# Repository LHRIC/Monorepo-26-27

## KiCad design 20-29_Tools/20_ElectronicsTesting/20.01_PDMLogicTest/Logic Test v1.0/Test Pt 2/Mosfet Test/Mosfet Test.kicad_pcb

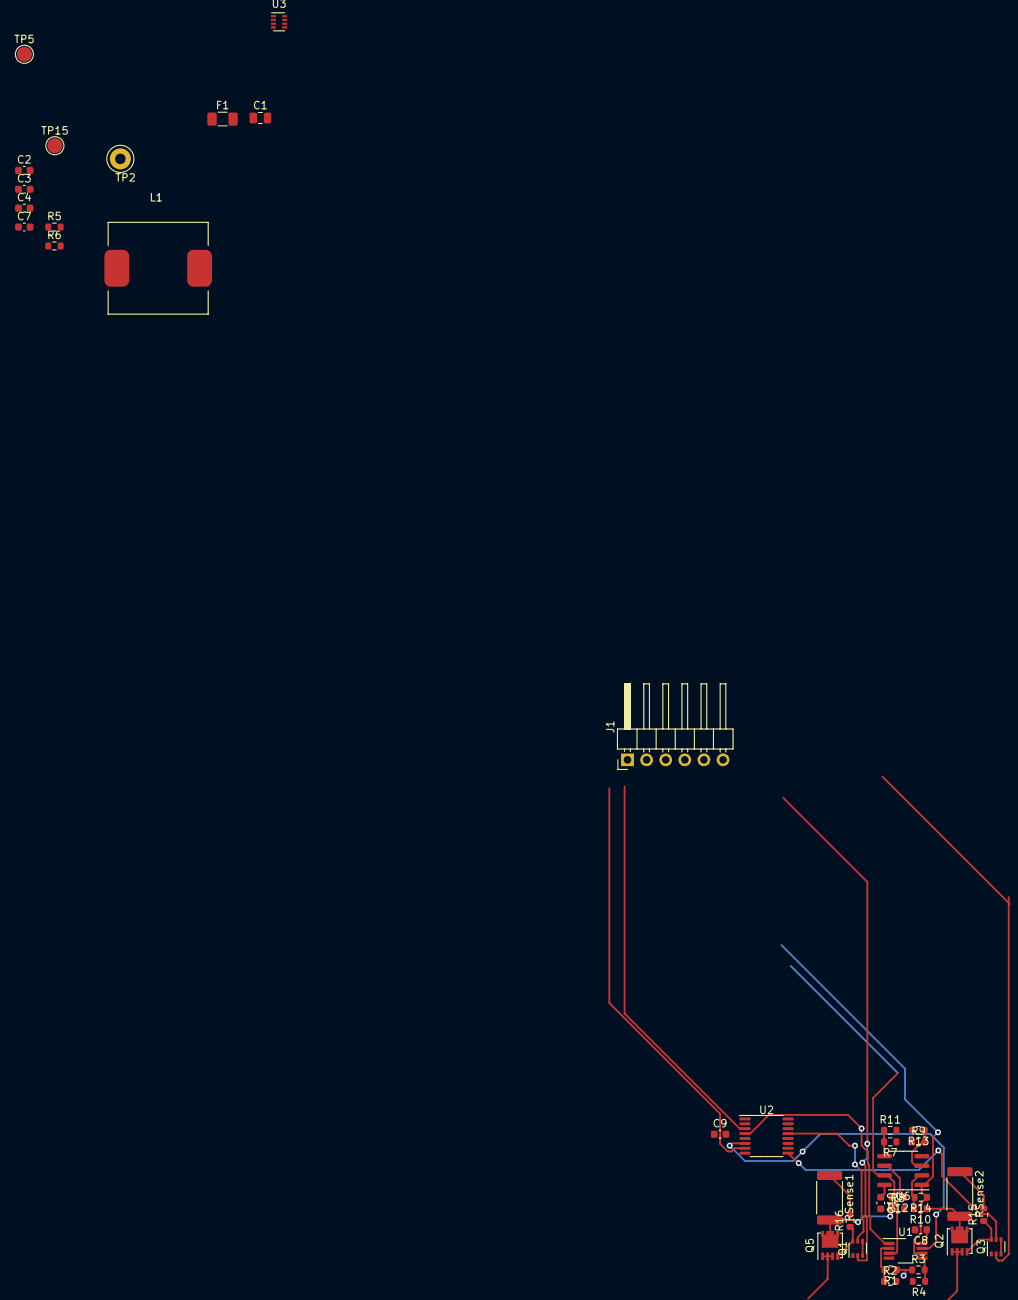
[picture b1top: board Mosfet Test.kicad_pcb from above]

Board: 2 copper layers, 40 parts (0 on the bottom side), 32 nets.

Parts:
C1: 10uF; C_0805_2012Metric
C2, C4: 0.1uF; C_0603_1608Metric
C3: 33nF; C_0603_1608Metric
C7: 47uF; C_0603_1608Metric
C8, C9, C10: C_Small; C_0603_1608Metric
F1: 750mA; Fuse_1206_3216Metric
J1: Conn_01x06_Pin; PinHeader_1x06_P2.54mm_Horizontal
L1: 5.6uH; HCMA1305-5R6-R
Q1, Q3: DMN63D8LDW; SOT-363_SC-70-6
Q2, Q5: SiS443DN; Vishay_PowerPAK_1212-8_Single
R1, R2, R3, R4, R7, R8, R9, R10, R11, R12, R13, R14: R_Small; R_0603_1608Metric
R5: 52.3k; R_0603_1608Metric
R6: 10k; R_0603_1608Metric
R15, R16: 100k; R_0603_1608Metric
RSense1, RSense2: R_Small; R_2512_6332Metric
TP2: TestPoint; TestPoint_Loop_D3.50mm_Drill1.4mm_Beaded
TP5, TP15: TP; TestPoint_Pad_D2.0mm
U1: TLV7012DGKR; VSSOP-8_3.0x3.0mm_P0.65mm
U2: CD4044B; TSSOP-16_4.4x5mm_P0.65mm
U3: TPS62933; SOT-583
U6: Opamp_Dual; SOIC-8_3.9x4.9mm_P1.27mm

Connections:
+5V: C8.1, C9.1, C10.1, F1.2, R1.1, R3.1, TP15.1, U1.8 (V+), U2.5 (Enable), U2.16 (V+), U6.8 (V+)
+12V: C1.1, C2.1, R7.1, R9.1, R15.2, R16.2, RSense1.1, RSense2.1, TP2.1, TP5.1, U3.3 (VIN)
/Drain: Q5.5 (D), R8.1, RSense1.2
/Fault: Q3.5 (G), U2.9 (Q)
/Load+: Q2.1 (S), Q2.2 (S), Q2.3 (S)
/Source: Q5.1 (S), Q5.2 (S), Q5.3 (S)
CS1: J1.3, R12.2, U1.3 (+), U6.7
CS2: J1.6, R14.1, U1.6 (-), U6.1
EN1: J1.2, Q1.2 (G)
EN2: J1.5, Q3.2 (G)
GND: C1.2, C2.2, C3.2, C7.2, C8.2, C9.2, C10.2, Q1.1 (S), Q3.1 (S), R2.2, R4.2, R6.2, R11.2, R13.2, U1.4 (V-), U2.8 (V-), U3.4 (GND), U6.4 (V-)
unnamed: C7.1, F1.1, L1.2, R5.1
unnamed: Q1.6 (D), Q5.4 (G), R16.1
unnamed: Q1.5 (G), U2.13 (Q)
unnamed: Q1.3 (D), Q1.4 (S)
unnamed: Q2.5 (D), R10.1, RSense2.2
unnamed: Q2.4 (G), Q3.6 (D), R15.1
unnamed: Q3.3 (D), Q3.4 (S)
unnamed: R1.2, R2.1, U1.2 (-)
unnamed: R3.2, R4.1, U1.5 (+)
unnamed: U1.1, U2.4 (R)
unnamed: U1.7, U2.6 (R)
unnamed: C4.1, U3.6 (BST)
unnamed: R5.2, R6.1, U3.8 (FB)
unnamed: C3.1, U3.7 (SS)
unnamed: C4.2, L1.1, U3.5 (SW)
unnamed: R9.2, R13.1, U6.3 (+)
unnamed: R10.2, R14.2, U6.2 (-)
unnamed: R7.2, R11.1, U6.5 (+)
unnamed: R8.2, R12.1, U6.6 (-)
Reset1: J1.1, U2.3 (S)
Reset2: J1.4, U2.7 (S)

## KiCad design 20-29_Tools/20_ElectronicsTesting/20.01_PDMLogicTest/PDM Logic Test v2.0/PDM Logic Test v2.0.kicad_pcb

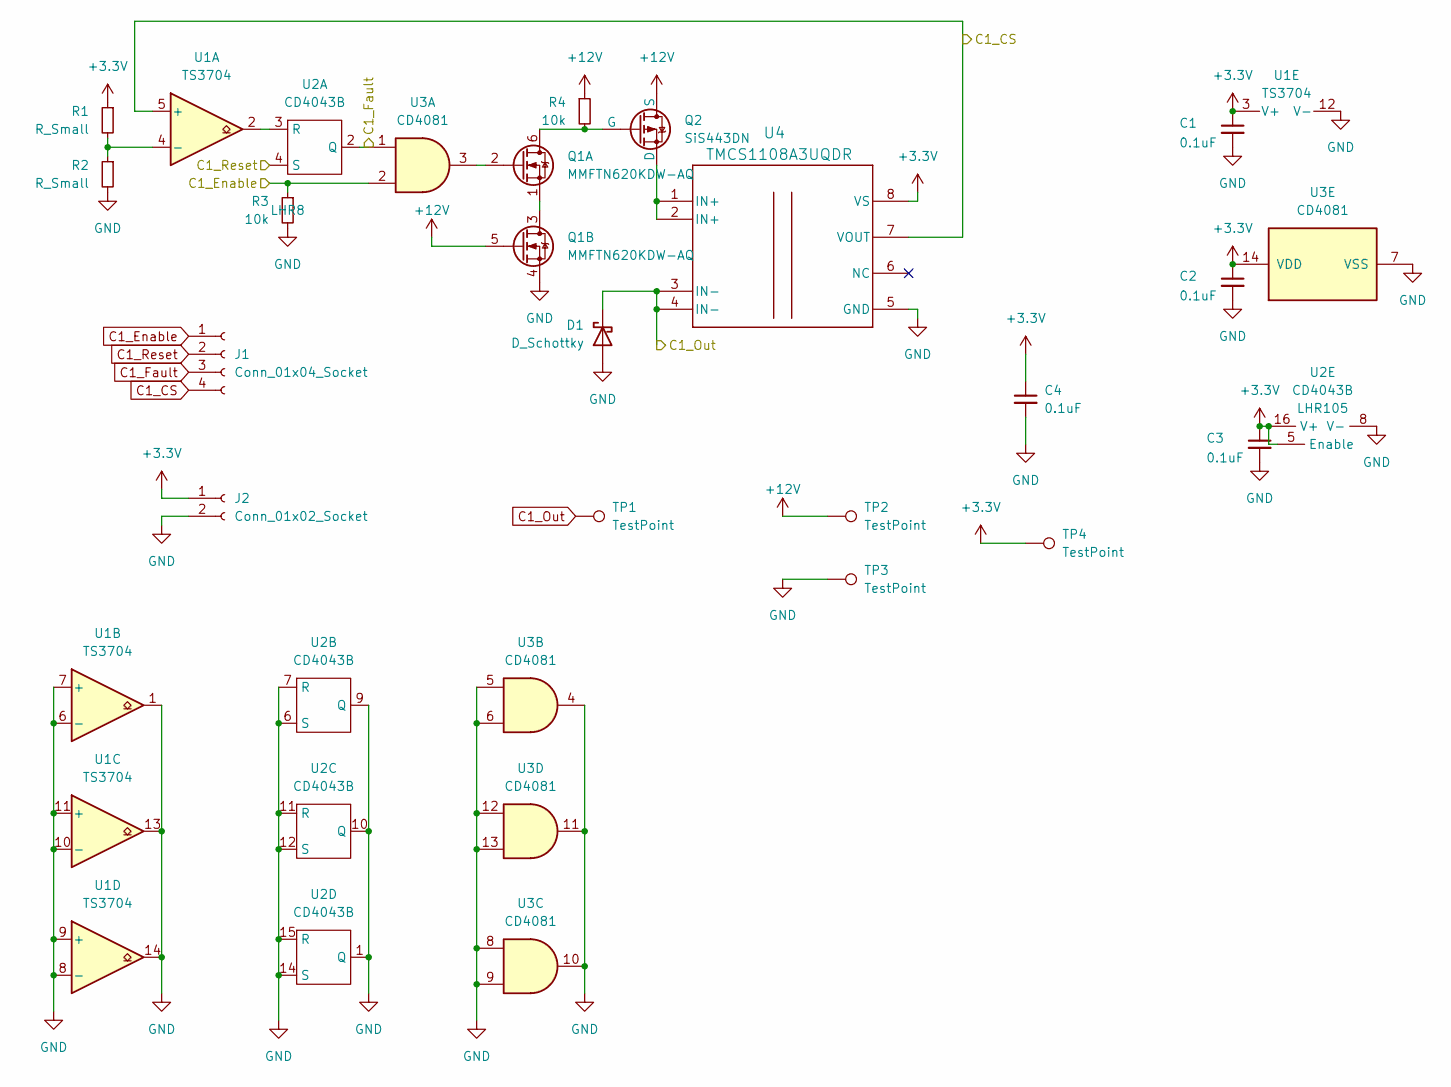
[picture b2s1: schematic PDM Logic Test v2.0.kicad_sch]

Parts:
C1, C2, C3, C4: 0.1uF; C_0603_1608Metric; LCSC C1591
D1: D_Schottky; D_SOD-523; LCSC C3758469
J1: Conn_01x04_Socket; PinHeader_1x04_P2.54mm_Vertical
J2: Conn_01x02_Socket; PinHeader_1x02_P2.54mm_Vertical
Q1: MMFTN620KDW-AQ; SOT-363_SC-70-6; LCSC C6226911
Q2: SiS443DN; Vishay_PowerPAK_1212-8_Single; LCSC C48586476
R1, R2: R_Small; R_0603_1608Metric
R3, R4: 10k; R_0603_1608Metric; LCSC C2479067
TP1, TP2: TestPoint; TestPoint_THTPad_D3.0mm_Drill1.5mm
TP3, TP4: TestPoint; TestPoint_Pad_D1.5mm
U1: TS3704; TSSOP-14_4.4x5mm_P0.65mm; LCSC C75832
U2: CD4043B; SOIC-16_3.9x9.9mm_P1.27mm
U3: CD4081; TSSOP-14_4.4x5mm_P0.65mm
U4: TMCS1108A3UQDR; SOIC-8_3.9x4.9mm_P1.27mm; LCSC C3684263

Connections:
+3.3V: C1.1, C2.1, C3.1, C4.1, J2.1, R1.1, TP4.1, U1.3 (V+), U2.5 (Enable), U2.16 (V+), U3.14 (VDD), U4.8 (VS)
+12V: Q1.5 (G), Q2.1 (S), Q2.2 (S), Q2.3 (S), R4.1, TP2.1
C1_CS: J1.4, U1.5 (+), U4.7 (VOUT)
C1_Enable: J1.1, R3.1, U3.2
C1_Fault: J1.3, U2.2 (Q), U3.1
C1_Out: D1.1 (K), TP1.1, U4.3 (IN-), U4.4 (IN-)
C1_Reset: J1.2, U2.4 (S)
GND: C1.2, C2.2, C3.2, C4.2, D1.2 (A), J2.2, Q1.4 (S), R2.2, R3.2, TP3.1, U1.1, U1.6 (-), U1.7 (+), U1.8 (-), U1.9 (+), U1.10 (-), U1.11 (+), U1.12 (V-), U1.13, U1.14, U2.1 (Q), U2.6 (S), U2.7 (R), U2.8 (V-), U2.9 (Q), U2.10 (Q), U2.11 (R), U2.12 (S), U2.14 (S), U2.15 (R), U3.4, U3.5, U3.6, U3.7 (VSS), U3.8, U3.9, U3.10, U3.11, U3.12, U3.13, U4.5 (GND)
unnamed: Q1.6 (D), Q2.4 (G), R4.2
unnamed: Q1.2 (G), U3.3
unnamed: Q1.1 (S), Q1.3 (D)
unnamed: Q2.5 (D), U4.1 (IN+), U4.2 (IN+)
unnamed: R1.2, R2.1, U1.4 (-)
unnamed: U1.2, U2.3 (R)

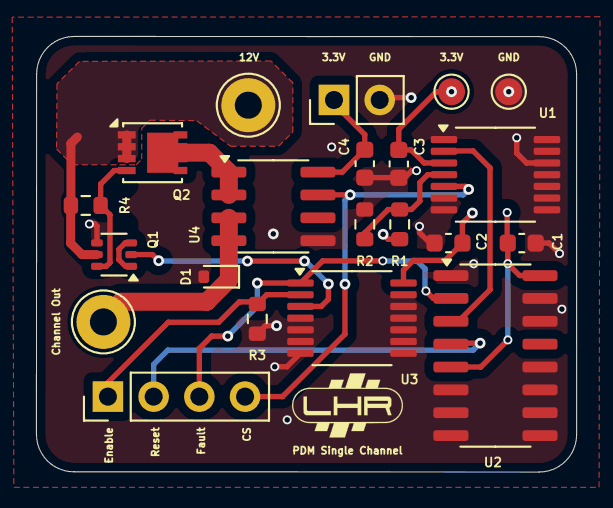
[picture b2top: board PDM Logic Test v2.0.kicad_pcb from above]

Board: 4 copper layers, 30.0 x 24.2 mm, 21 parts (0 on the bottom side), 14 nets.

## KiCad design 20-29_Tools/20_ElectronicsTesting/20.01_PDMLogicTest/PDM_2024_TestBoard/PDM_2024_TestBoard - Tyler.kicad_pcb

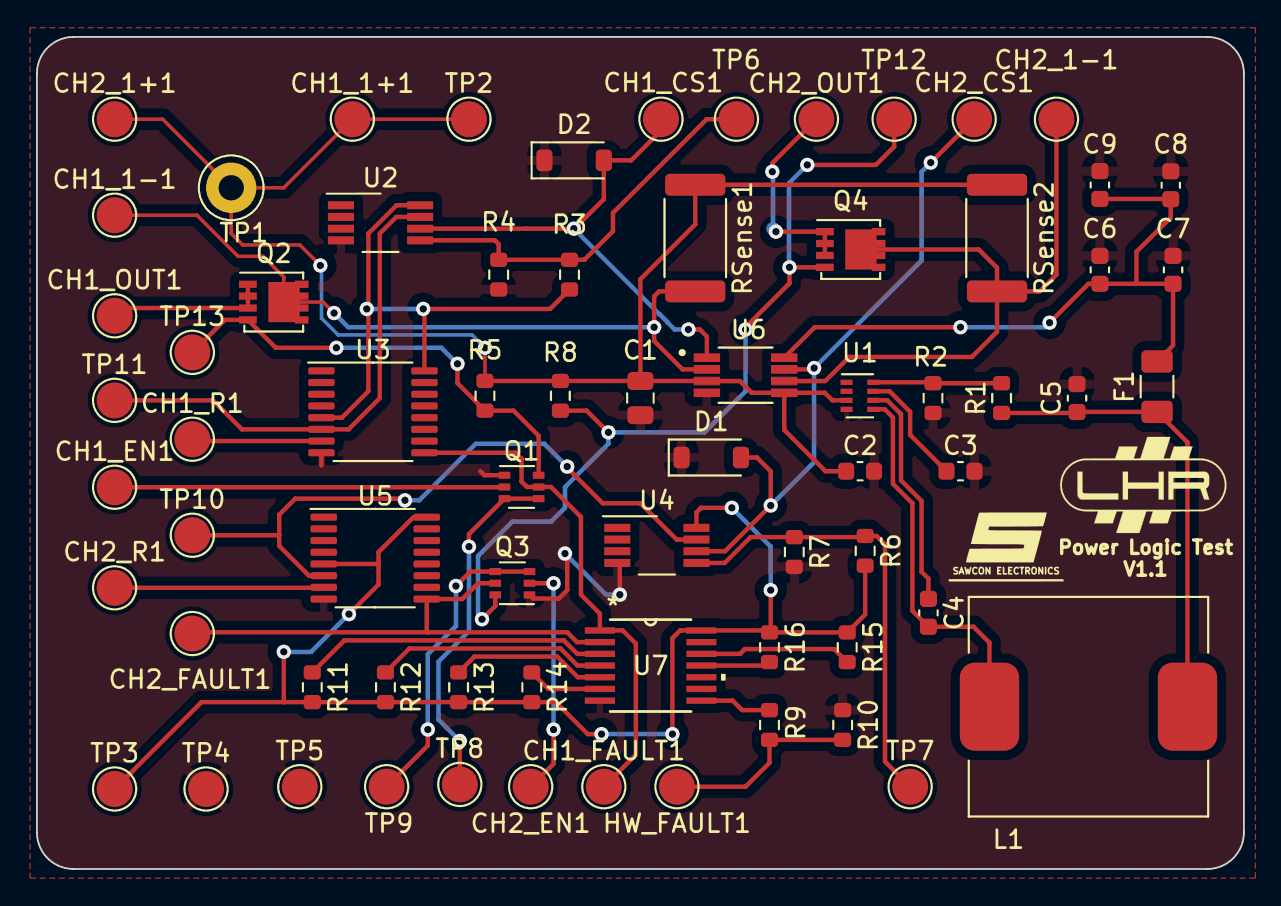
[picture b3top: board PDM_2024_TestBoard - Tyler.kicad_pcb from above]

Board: 4 copper layers, 67.1 x 46.2 mm, 70 parts (0 on the bottom side), 36 nets.

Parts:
C1: 10uF; C_0805_2012Metric
C2, C4: 0.1uF; C_0603_1608Metric
C3: 33nF; C_0603_1608Metric
C5: 47uF; C_0603_1608Metric
C6, C7, C8, C9: C_Small; C_0603_1608Metric
CH1_1+1, CH1_1-1, CH1_CS1, CH1_EN1, CH1_FAULT1, CH1_OUT1, CH1_R1, CH2_1+1, CH2_1-1, CH2_CS1, CH2_EN1, CH2_FAULT1, CH2_OUT1, CH2_R1: TP; TestPoint_Pad_D2.0mm
D1, D2: D_Zener; D_SOD-123
F1: 750mA; Fuse_1206_3216Metric
HW_FAULT1: TP; TestPoint_Pad_D2.0mm
L1: 5.6uH; HCMA1305-5R6-R
Q1, Q3: DMN63D8LDW; SOT-363_SC-70-6
Q2, Q4: SiS443DN; Vishay_PowerPAK_1212-8_Single
R1: 52.3k; R_0603_1608Metric
R2, R9, R11, R12, R13, R14, R15, R16: 10k; R_0603_1608Metric
R3, R4, R6, R7: R_Small; R_0603_1608Metric
R5, R8: 100k; R_0603_1608Metric
R10: 16k; R_0603_1608Metric
RSense1, RSense2: R_Small; R_2512_6332Metric
TP1: TestPoint; TestPoint_Loop_D3.50mm_Drill1.4mm_Beaded
TP2, TP3, TP4, TP5, TP6, TP7, TP8, TP9, TP10, TP11, TP12, TP13: TP; TestPoint_Pad_D2.0mm
U1: TPS62933; SOT-583
U2, U4: TLV7012DGKR; VSSOP-8_3.0x3.0mm_P0.65mm
U3, U5: CD4044B; TSSOP-16_4.4x5mm_P0.65mm
U6: INA2180A1IDGKT; SOP65P490X110-8N
U7: CD74HC30PWR; PW14

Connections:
+5V: C6.1, C7.1, C8.1, C9.1, F1.2, R3.2, R6.2, R11.2, R12.2, R13.2, R14.2, R15.1, R16.1, TP3.1, U2.8 (V+), U3.5 (Enable), U3.16 (V+), U4.8 (V+), U5.5 (Enable), U5.16 (V+), U6.8 (VS), U7.14 (VCC)
CH1_1+: C1.1, C2.1, CH1_1+1.1, CH2_1+1.1, R5.2, R8.2, RSense1.1, RSense2.1, TP1.1, TP2.1, U1.3 (VIN), U6.3 (IN+1), U6.5 (IN+2)
CH1_1-: CH1_1-1.1, Q2.5 (D), RSense1.2, U6.2 (IN-1)
CH1_CS: CH1_CS1.1, D2.2 (A), U2.6 (-), U6.1 (OUT1)
CH1_EN: CH1_EN1.1, Q1.2 (G)
CH1_Fault: CH1_FAULT1.1, Q1.5 (G), U3.9 (Q), U7.1 (A)
CH1_OUT: CH1_OUT1.1, Q2.1 (S), Q2.2 (S), Q2.3 (S)
CH1_R: CH1_R1.1, U3.7 (S)
CH2_1-: CH2_1-1.1, Q4.5 (D), RSense2.2, U6.6 (IN-2)
CH2_CS: CH2_CS1.1, D1.2 (A), U4.6 (-), U6.7 (OUT2)
CH2_EN: CH2_EN1.1, Q3.2 (G)
CH2_Fault: CH2_FAULT1.1, Q3.5 (G), U5.9 (Q), U7.2 (B)
CH2_OUT: CH2_OUT1.1, Q4.1 (S), Q4.2 (S), Q4.3 (S)
CH2_R: CH2_R1.1, U5.7 (S)
GND: C1.2, C2.2, C3.2, C5.2, C6.2, C7.2, C8.2, C9.2, D1.1 (K), D2.1 (K), Q1.1 (S), Q3.1 (S), R2.2, R4.2, R7.2, R10.1, TP4.1, TP5.1, U1.4 (GND), U2.4 (V-), U3.8 (V-), U4.4 (V-), U5.8 (V-), U6.4 (GND), U7.7 (GND)
HW1_Fault: HW_FAULT1.1, R9.1, R10.2
unnamed: C5.1, F1.1, L1.2, R1.1
unnamed: Q1.6 (D), Q2.4 (G), R5.1, TP13.1
unnamed: Q1.3 (D), Q1.4 (S), TP8.1
unnamed: Q3.6 (D), Q4.4 (G), R8.1, TP12.1
unnamed: Q3.3 (D), Q3.4 (S), TP9.1
unnamed: C4.1, U1.6 (BST)
unnamed: R1.2, R2.1, U1.8 (FB)
unnamed: C3.1, U1.7 (SS)
unnamed: C4.2, L1.1, U1.5 (SW)
unnamed: R3.1, R4.1, TP6.1, U2.5 (+)
unnamed: TP11.1, U2.7, U3.6 (R)
unnamed: R6.1, R7.1, TP7.1, U4.5 (+)
unnamed: TP10.1, U4.7, U5.6 (R)
unnamed: R9.2, U7.8 (*Y)
unnamed: R11.1, U7.3 (C)
unnamed: R12.1, U7.4 (D)
unnamed: R13.1, U7.5 (E)
unnamed: R14.1, U7.6 (F)
unnamed: R16.2, U7.11 (G)
unnamed: R15.2, U7.12 (H)

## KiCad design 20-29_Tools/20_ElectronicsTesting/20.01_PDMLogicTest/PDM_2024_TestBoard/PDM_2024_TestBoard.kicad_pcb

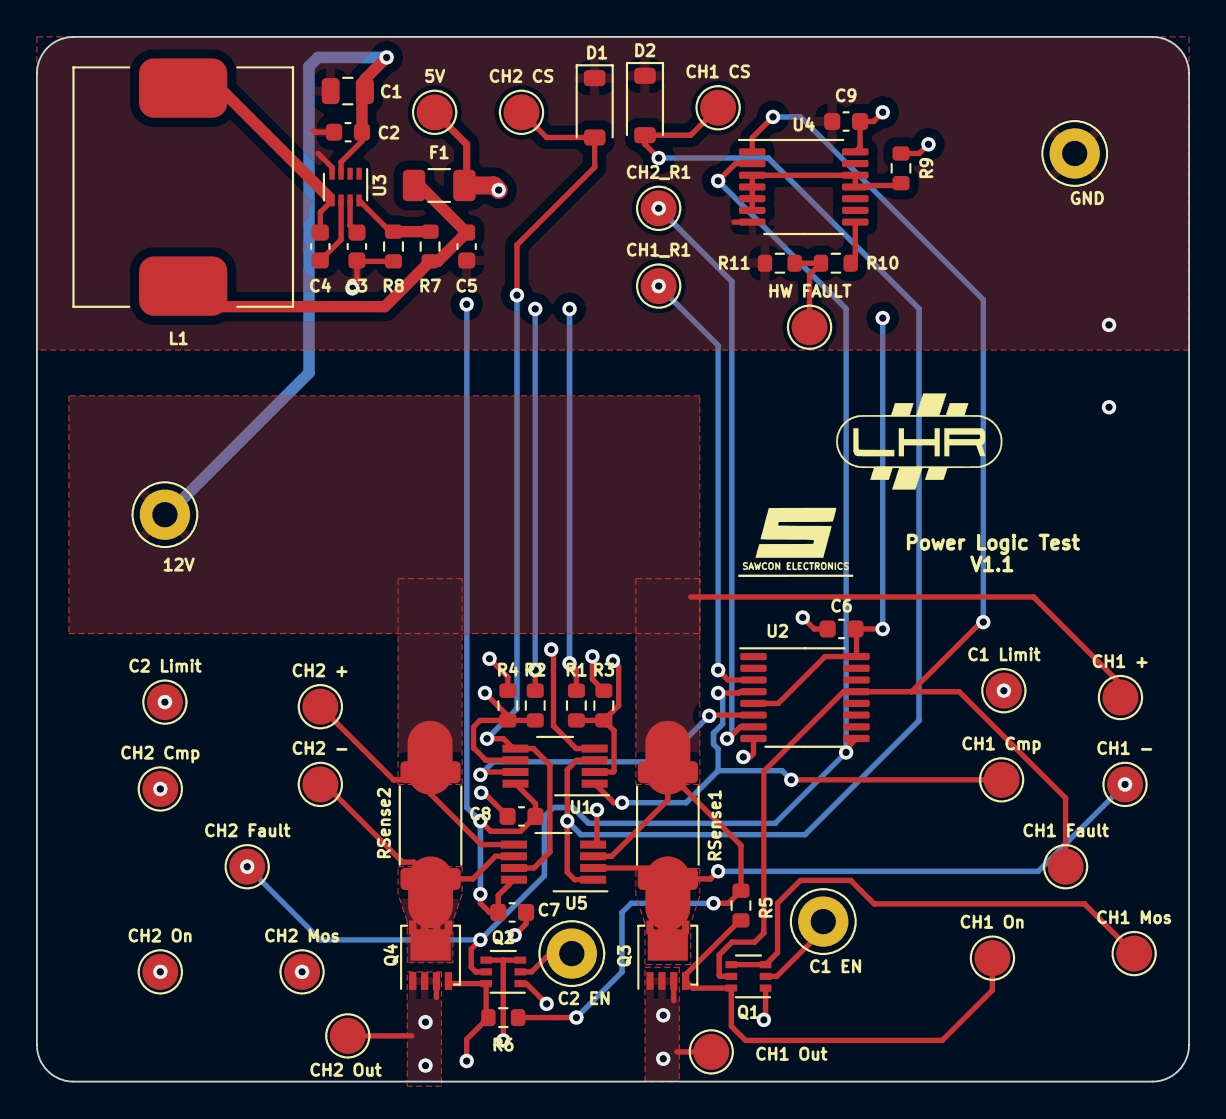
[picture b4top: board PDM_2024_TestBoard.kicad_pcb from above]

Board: 4 copper layers, 64.0 x 58.0 mm, 61 parts (0 on the bottom side), 31 nets.

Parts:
5V: TP; TestPoint_Pad_D2.0mm
12V: TestPoint; TestPoint_Loop_D3.50mm_Drill1.4mm_Beaded
C1: 10uF; C_0805_2012Metric
C1 EN, C2 EN: TestPoint; TestPoint_Loop_D3.50mm_Drill1.4mm_Beaded
C1 Limit, C2 Limit: TP; TestPoint_Pad_D2.0mm
C2, C4: 0.1uF; C_0603_1608Metric
C3: 33nF; C_0603_1608Metric
C5: 47uF; C_0603_1608Metric
C6, C7, C8, C9: C_Small; C_0603_1608Metric
CH1 +, CH1 -, CH1 CS, CH1 Cmp, CH1 Fault, CH1 Mos, CH1 On, CH1 Out, CH1_R1, CH2 +, CH2 -, CH2 CS, CH2 Cmp, CH2 Fault, CH2 Mos, CH2 On, CH2 Out, CH2_R1: TP; TestPoint_Pad_D2.0mm
D1, D2: D_Zener; D_SOD-123
F1: 750mA; Fuse_1206_3216Metric
GND: GND; TestPoint_Loop_D3.50mm_Drill1.4mm_Beaded
HW FAULT: TP; TestPoint_Pad_D2.0mm
L1: 5.6uH; HCMA1305-5R6-R
Q1, Q2: DMN63D8LDW; SOT-363_SC-70-6
Q3, Q4: SiS443DN; Vishay_PowerPAK_1212-8_Single
R1, R2, R3, R4: R_Small; R_0603_1608Metric
R5, R6: 100k; R_0603_1608Metric
R7: 52.3k; R_0603_1608Metric
R8, R9, R10: 10k; R_0603_1608Metric
R11: 16k; R_0603_1608Metric
RSense1, RSense2: R_Small; R_2512_6332Metric
U1: TLV7012DGKR; VSSOP-8_3.0x3.0mm_P0.65mm
U2: CD4044B; TSSOP-16_4.4x5mm_P0.65mm
U3: TPS62933; SOT-583
U4: CD74HC30PWR; TSSOP-14_4.4x5mm_P0.65mm
U5: INA2180A1IDGKT; VSSOP-8_3.0x3.0mm_P0.65mm

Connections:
+5V: 5V.1, C6.1, C7.1, C8.1, C9.2, F1.2, R1.2, R2.2, R9.1, U1.8 (V+), U2.5 (Enable), U2.16 (V+), U4.14 (VCC), U5.8 (VS)
+12V: 12V.1, C1.1, C2.1, CH1 +.1, CH2 +.1, R5.2, R6.2, RSense1.1, RSense2.1, U3.3 (VIN), U5.3 (IN+1), U5.5 (IN+2)
CH1-: CH1 -.1, Q3.5 (D), RSense1.2, U5.2 (IN-1)
CH1_CS: CH1 CS.1, D2.2 (A), U1.3 (+), U5.1 (OUT1)
CH1_EN: C1 EN.1, Q1.2 (G)
CH1_Fault: CH1 Fault.1, Q1.5 (G), U2.13 (Q), U4.1 (A)
CH1_OUT: CH1 Out.1, Q3.1 (S), Q3.2 (S), Q3.3 (S)
CH1_R: CH1_R1.1, U2.3 (S)
CH2-: CH2 -.1, Q4.5 (D), RSense2.2, U5.6 (IN-2)
CH2_CS: CH2 CS.1, D1.2 (A), U1.5 (+), U5.7 (OUT2)
CH2_EN: C2 EN.1, Q2.2 (G)
CH2_Fault: CH2 Fault.1, Q2.5 (G), U2.9 (Q), U4.2 (B)
CH2_OUT: CH2 Out.1, Q4.1 (S), Q4.2 (S), Q4.3 (S)
CH2_R: CH2_R1.1, U2.7 (S)
GND: C1.2, C2.2, C3.2, C5.2, C6.2, C7.2, C8.2, C9.1, D1.1 (K), D2.1 (K), GND.1, Q1.1 (S), Q2.1 (S), R3.2, R4.2, R8.2, R11.1, U1.4 (V-), U2.8 (V-), U3.4 (GND), U4.7 (GND), U5.4 (GND)
HW_Fault: HW FAULT.1, R10.1, R11.2
unnamed: C5.1, F1.1, L1.2, R7.1
unnamed: CH1 On.1, Q1.6 (D), Q3.4 (G), R5.1
unnamed: CH1 Mos.1, Q1.3 (D), Q1.4 (S)
unnamed: CH2 On.1, Q2.6 (D), Q4.4 (G), R6.1
unnamed: CH2 Mos.1, Q2.3 (D), Q2.4 (S)
unnamed: C1 Limit.1, R1.1, R3.1, U1.2 (-)
unnamed: C2 Limit.1, R2.1, R4.1, U1.6 (-)
unnamed: CH1 Cmp.1, U1.1, U2.4 (R)
unnamed: CH2 Cmp.1, U1.7, U2.6 (R)
unnamed: C4.1, U3.6 (BST)
unnamed: R7.2, R8.1, U3.8 (FB)
unnamed: C3.1, U3.7 (SS)
unnamed: C4.2, L1.1, U3.5 (SW)
unnamed: R10.2, U4.8 (*Y)
unnamed: R9.2, U4.3 (C), U4.4 (D), U4.5 (E), U4.6 (F), U4.11 (G), U4.12 (H)

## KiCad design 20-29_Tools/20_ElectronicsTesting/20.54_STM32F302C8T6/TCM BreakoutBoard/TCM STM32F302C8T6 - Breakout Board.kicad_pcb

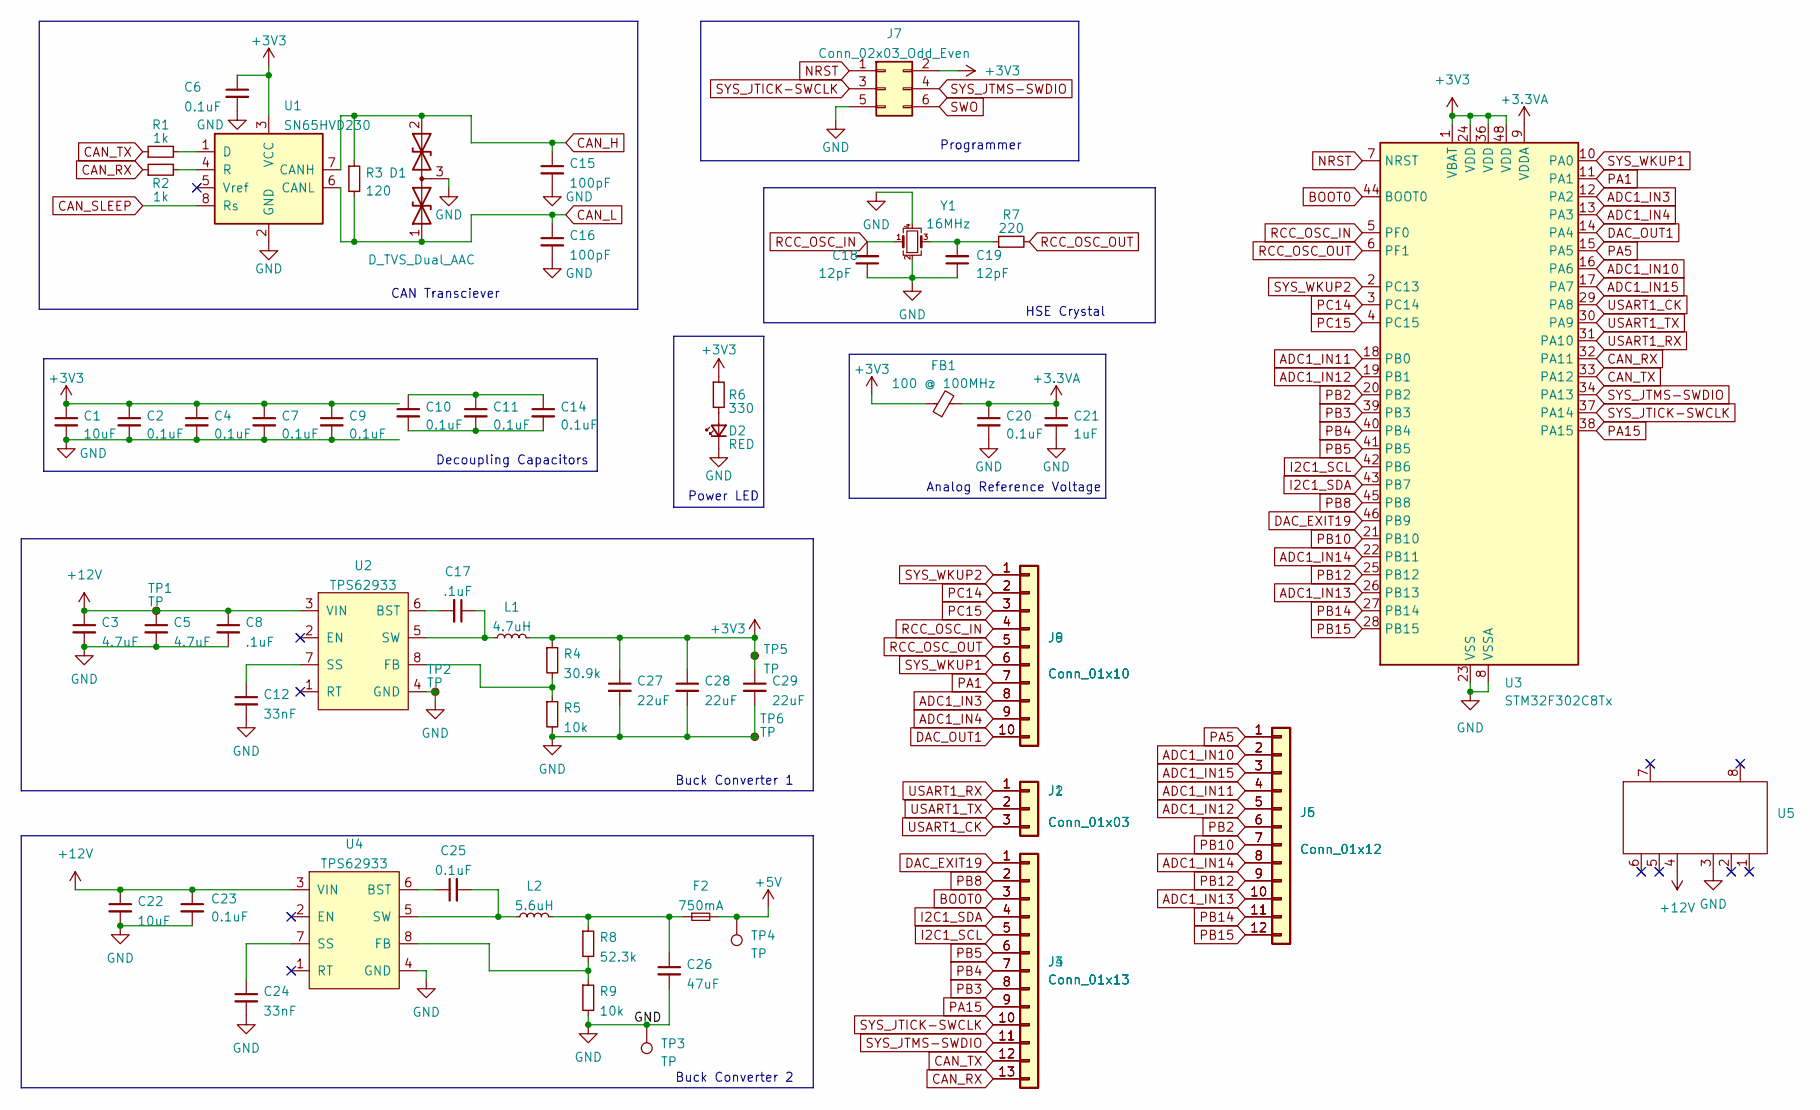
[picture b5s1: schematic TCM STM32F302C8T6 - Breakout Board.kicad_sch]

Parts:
C1: 10uF; C_0805_2012Metric
C2, C4, C6, C7, C9, C10, C11, C14, C20, C23, C25: 0.1uF; C_0603_1608Metric
C3, C5: 4.7uF; C_0805_2012Metric
C8, C17: .1uF; C_0603_1608Metric
C12, C24: 33nF; C_0603_1608Metric
C15, C16: 100pF; C_0603_1608Metric
C18, C19: 12pF; C_0402_1005Metric
C21: 1uF; C_0603_1608Metric
C22: 10uF; C_0603_1608Metric
C26: 47uF; C_0603_1608Metric
C27, C28, C29: 22uF; C_0805_2012Metric
D1: D_TVS_Dual_AAC; SOT-23
D2: RED; LED_0603_1608Metric
F2: 750mA; Fuse_1206_3216Metric
FB1: 100 @ 100MHz; C_0402_1005Metric
J1: Conn_01x03; PinSocket_1x03_P2.54mm_Vertical
J2: Conn_01x03; PinHeader_1x03_P2.54mm_Vertical
J3: Conn_01x13; PinSocket_1x13_P2.54mm_Vertical
J4: Conn_01x13; PinHeader_1x13_P2.54mm_Vertical
J5: Conn_01x12; PinHeader_1x12_P2.54mm_Vertical
J6: Conn_01x12; PinSocket_1x12_P2.54mm_Vertical
J7: Conn_02x03_Odd_Even; Molex_Micro-Fit_3.0_43045-0612_2x03_P3.00mm_Vertical
J8: Conn_01x10; PinHeader_1x10_P2.54mm_Vertical
J9: Conn_01x10; PinSocket_1x10_P2.54mm_Vertical
L1: 4.7uH; SRU8043-4R7Y
L2: 5.6uH; HCMA1305-5R6-R
R1, R2: 1k; R_0603_1608Metric
R3: 120; R_0603_1608Metric
R4: 30.9k; R_0603_1608Metric
R5, R9: 10k; R_0603_1608Metric
R6: 330; R_0603_1608Metric
R7: 220; R_0603_1608Metric
R8: 52.3k; R_0603_1608Metric
TP1, TP2, TP3, TP4, TP5, TP6: TP; TestPoint_Pad_D2.0mm
U1: SN65HVD230; SOIC-8_3.9x4.9mm_P1.27mm
U2, U4: TPS62933; SOT-583
U3: STM32F302C8Tx; LQFP-48_7x7mm_P0.5mm
U5: Adafruit HUSB238 USB PD
Y1: 16MHz; Crystal_SMD_3225-4Pin_3.2x2.5mm

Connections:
+3.3VA: C20.1, C21.1, FB1.2, U3.9 (VDDA)
+5V: F2.2, TP4.1
+12V: C3.1, C5.1, C8.1, C22.1, C23.1, TP1.1, U2.3 (VIN), U4.3 (VIN), U5.4
ADC1_IN3: J8.8, J9.8, U3.12 (PA2)
ADC1_IN4: J8.9, J9.9, U3.13 (PA3)
ADC1_IN10: J5.2, J6.2, U3.16 (PA6)
ADC1_IN11: J5.4, J6.4, U3.18 (PB0)
ADC1_IN12: J5.5, J6.5, U3.19 (PB1)
ADC1_IN13: J5.10, J6.10, U3.26 (PB13)
ADC1_IN14: J5.8, J6.8, U3.22 (PB11)
ADC1_IN15: J5.3, J6.3, U3.17 (PA7)
BOOT0: J3.3, J4.3, U3.44 (BOOT0)
CAN_H: C15.1, D1.2 (A2), R3.1, U1.7 (CANH)
CAN_L: C16.1, D1.1 (A1), R3.2, U1.6 (CANL)
CAN_RX: J3.13, J4.13, R2.1, U3.32 (PA11)
CAN_SLEEP: U1.8 (Rs)
CAN_TX: J3.12, J4.12, R1.1, U3.33 (PA12)
DAC_EXIT19: J3.1, J4.1, U3.46 (PB9)
DAC_OUT1: J8.10, J9.10, U3.14 (PA4)
I2C1_SCL: J3.5, J4.5, U3.42 (PB6)
I2C1_SDA: J3.4, J4.4, U3.43 (PB7)
NRST: J7.1, U3.7 (NRST)
unnamed: C19.2, R7.1, Y1.3
unnamed: C26.1, F2.1, L2.2, R8.1
unnamed: D2.2 (A), R6.2
unnamed: R1.2, U1.1 (D)
unnamed: R2.2, U1.4 (R)
unnamed: C17.2, U2.6 (BST)
unnamed: R4.2, R5.1, U2.8 (FB)
unnamed: C12.1, U2.7 (SS)
unnamed: C17.1, L1.1, U2.5 (SW)
unnamed: C25.1, U4.6 (BST)
unnamed: R8.2, R9.1, U4.8 (FB)
unnamed: C24.1, U4.7 (SS)
unnamed: C25.2, L2.1, U4.5 (SW)
PA1: J8.7, J9.7, U3.11 (PA1)
PA5: J5.1, J6.1, U3.15 (PA5)
PA15: J3.9, J4.9, U3.38 (PA15)
PB2: J5.6, J6.6, U3.20 (PB2)
PB3: J3.8, J4.8, U3.39 (PB3)
PB4: J3.7, J4.7, U3.40 (PB4)
PB5: J3.6, J4.6, U3.41 (PB5)
PB8: J3.2, J4.2, U3.45 (PB8)
PB10: J5.7, J6.7, U3.21 (PB10)
PB12: J5.9, J6.9, U3.25 (PB12)
PB14: J5.11, J6.11, U3.27 (PB14)
PB15: J5.12, J6.12, U3.28 (PB15)
PC14: J8.2, J9.2, U3.3 (PC14)
PC15: J8.3, J9.3, U3.4 (PC15)
RCC_OSC_IN: C18.2, J8.4, J9.4, U3.5 (PF0), Y1.1
RCC_OSC_OUT: J8.5, J9.5, R7.2, U3.6 (PF1)
SWO: J7.6
SYS_JTICK-SWCLK: J3.10, J4.10, J7.3, U3.37 (PA14)
SYS_JTMS-SWDIO: J3.11, J4.11, J7.4, U3.34 (PA13)
SYS_WKUP1: J8.6, J9.6, U3.10 (PA0)
SYS_WKUP2: J8.1, J9.1, U3.2 (PC13)
USART1_CK: J1.3, J2.3, U3.29 (PA8)
USART1_RX: J1.1, J2.1, U3.31 (PA10)
USART1_TX: J1.2, J2.2, U3.30 (PA9)

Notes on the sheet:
CAN Transciever
Power LED
HSE Crystal
Programmer
Decoupling Capacitors
Analog Reference Voltage
Buck Converter 2
Buck Converter 1

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
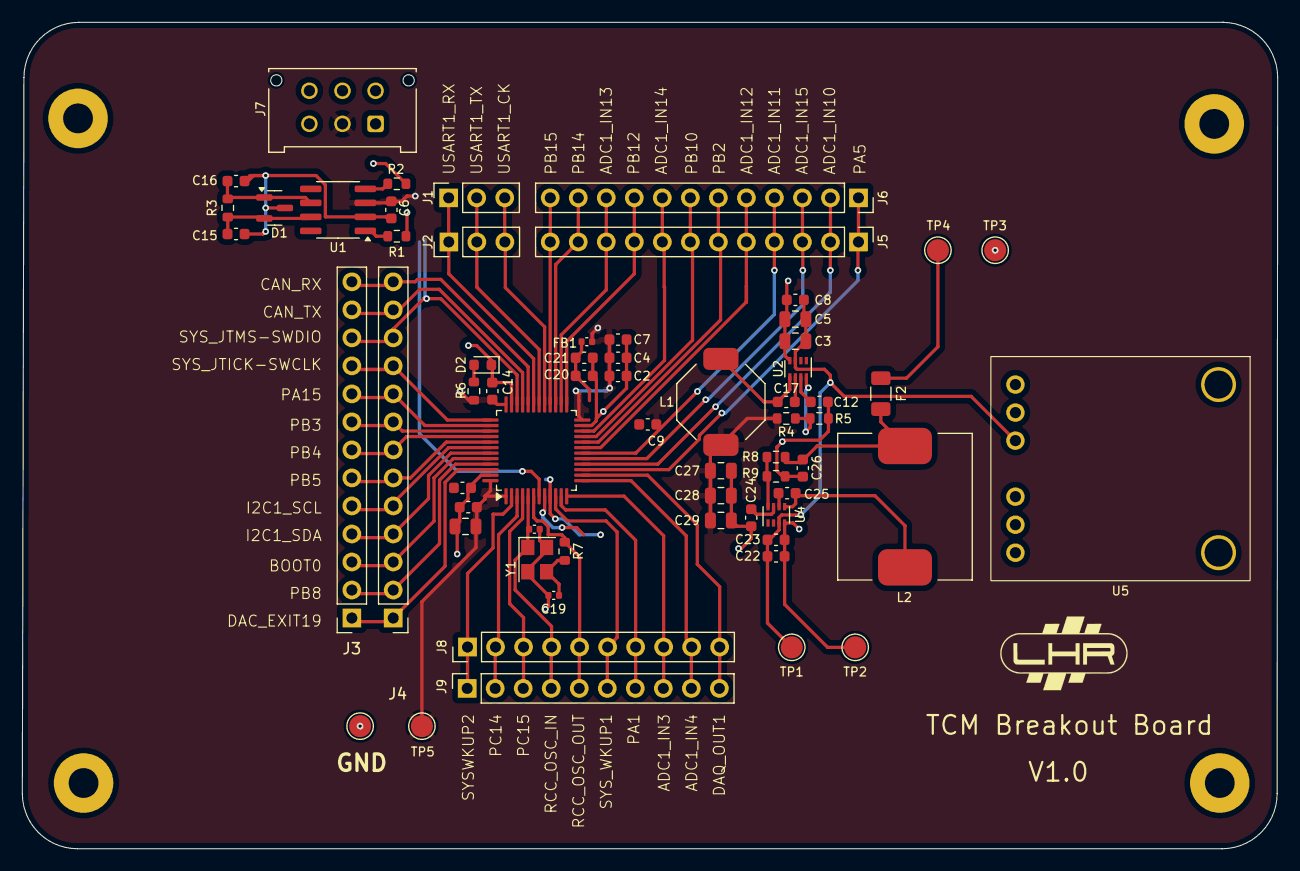
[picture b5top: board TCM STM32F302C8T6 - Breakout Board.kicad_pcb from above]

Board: 2 copper layers, 113.8 x 74.9 mm, 65 parts (0 on the bottom side), 59 nets.

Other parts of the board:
LHR: LOGO; LHR_medium

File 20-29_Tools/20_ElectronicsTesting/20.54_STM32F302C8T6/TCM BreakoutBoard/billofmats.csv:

"Reference","Value","Datasheet","Footprint","Qty","DNP"
"C1,C22","10uF","~","-- mixed values --","2",""
"C2,C4,C6,C7,C9,C10,C11,C14,C20,C23,C25","0.1uF","~","Capacitor_SMD:C_0603_1608Metric","11",""
"C3,C5","4.7uF","~","Capacitor_SMD:C_0805_2012Metric","2",""
"C8,C17",".1uF","~","Capacitor_SMD:C_0603_1608Metric","2",""
"C12,C24","33nF","~","Capacitor_SMD:C_0603_1608Metric","2",""
"C15,C16","100pF","~","Capacitor_SMD:C_0603_1608Metric","2",""
"C18,C19","12pF","~","Capacitor_SMD:C_0402_1005Metric","2",""
"C21","1uF","~","Capacitor_SMD:C_0603_1608Metric","1",""
"C26","47uF","~","Capacitor_SMD:C_0603_1608Metric","1",""
"C27,C28,C29","22uF","~","Capacitor_SMD:C_0805_2012Metric","3",""
"D1","D_TVS_Dual_AAC","~","Package_TO_SOT_SMD:SOT-23","1",""
"D2","RED","~","LED_SMD:LED_0603_1608Metric","1",""
"F2","750mA","~","Fuse:Fuse_1206_3216Metric","1",""
"FB1","100 @ 100MHz","~","Capacitor_SMD:C_0402_1005Metric","1",""
"J1,J2","Conn_01x03","~","-- mixed values --","2",""
"J3,J4","Conn_01x13","~","-- mixed values --","2",""
"J5,J6","Conn_01x12","~","-- mixed values --","2",""
"J7","Conn_02x03_Odd_Even","~","Connector_Molex:Molex_Micro-Fit_3.0_43045-0612_2x03_P3.00mm_Vertical","1",""
"J8,J9","Conn_01x10","~","-- mixed values --","2",""
"L1","4.7uH","~","LHR:SRU8043-4R7Y","1",""
"L2","5.6uH","~","LHR:HCMA1305-5R6-R","1",""
"R1,R2","1k","~","Resistor_SMD:R_0603_1608Metric","2",""
"R3","120","~","Resistor_SMD:R_0603_1608Metric","1",""
"R4","30.9k","~","Resistor_SMD:R_0603_1608Metric","1",""
"R5,R9","10k","~","Resistor_SMD:R_0603_1608Metric","2",""
"R6","330","~","Resistor_SMD:R_0603_1608Metric","1",""
"R7","220","~","Resistor_SMD:R_0603_1608Metric","1",""
"R8","52.3k","~","Resistor_SMD:R_0603_1608Metric","1",""
"TP1,TP2,TP3,TP4,TP5,TP6","TP","~","TestPoint:TestPoint_Pad_D2.0mm","6",""
"U1","SN65HVD230","http://www.ti.com/lit/ds/symlink/sn65hvd230.pdf","Package_SO:SOIC-8_3.9x4.9mm_P1.27mm","1",""
"U2,U4","TPS62933","","LHR:SOT-583","2",""
"U3","STM32F302C8Tx","https://www.st.com/resource/en/datasheet/stm32f302c8.pdf","Package_QFP:LQFP-48_7x7mm_P0.5mm","1",""
"U5","~","","LHR:Adafruit HUSB238 USB PD","1",""
"Y1","16MHz","~","Crystal:Crystal_SMD_3225-4Pin_3.2x2.5mm","1",""

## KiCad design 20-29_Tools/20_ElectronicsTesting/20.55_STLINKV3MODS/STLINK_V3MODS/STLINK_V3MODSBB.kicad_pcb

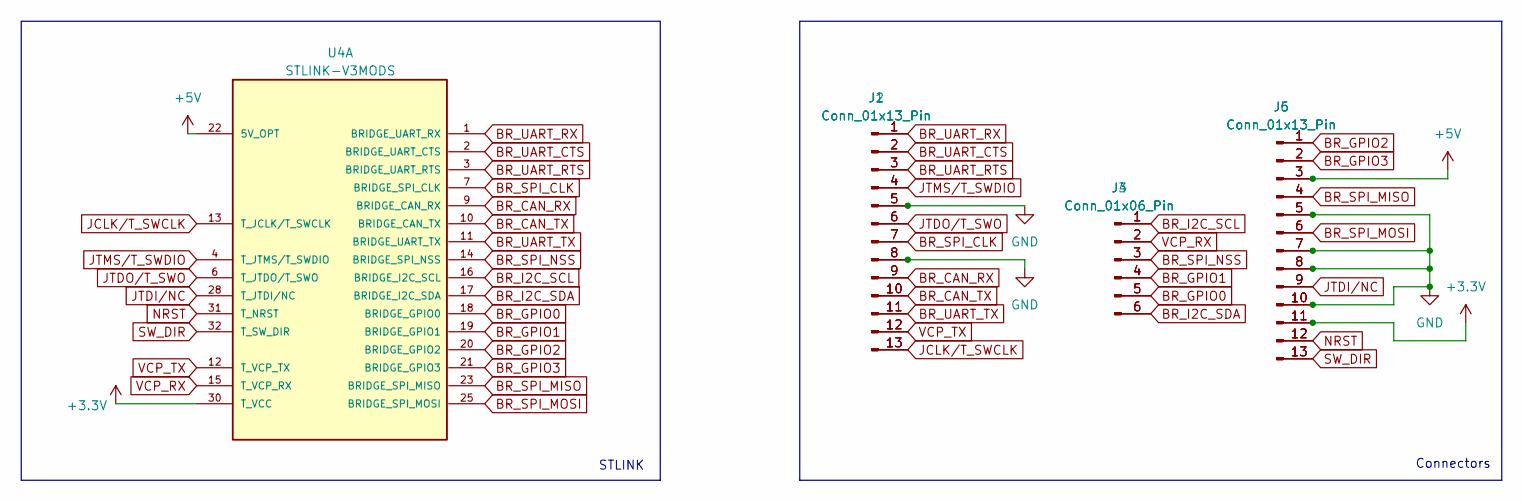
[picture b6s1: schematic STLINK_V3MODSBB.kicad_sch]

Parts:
J1, J2, J5, J6: Conn_01x13_Pin; PinHeader_1x13_P2.54mm_Vertical
J3, J4: Conn_01x06_Pin; PinHeader_1x06_P2.54mm_Vertical
U4: STLINK-V3MODS; MODULE_STLINK-V3MODS; PARTREV 1; DigiKey_Part_Number 497-STLINK-V3MODS-ND

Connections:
+3.3V: J5.11, J6.11, U4.30 (T_VCC)
+5V: J5.3, J6.3, U4.22 (5V_OPT)
BR_CAN_RX: J1.9, J2.9, U4.9 (BRIDGE_CAN_RX)
BR_CAN_TX: J1.10, J2.10, U4.10 (BRIDGE_CAN_TX)
BR_GPIO0: J3.5, J4.5, U4.18 (BRIDGE_GPIO0)
BR_GPIO1: J3.4, J4.4, U4.19 (BRIDGE_GPIO1)
BR_GPIO2: J5.1, J6.1, U4.20 (BRIDGE_GPIO2)
BR_GPIO3: J5.2, J6.2, U4.21 (BRIDGE_GPIO3)
BR_I2C_SCL: J3.1, J4.1, U4.16 (BRIDGE_I2C_SCL)
BR_I2C_SDA: J3.6, J4.6, U4.17 (BRIDGE_I2C_SDA)
BR_SPI_CLK: J1.7, J2.7, U4.7 (BRIDGE_SPI_CLK)
BR_SPI_MISO: J5.4, J6.4, U4.23 (BRIDGE_SPI_MISO)
BR_SPI_MOSI: J5.6, J6.6, U4.25 (BRIDGE_SPI_MOSI)
BR_SPI_NSS: J3.3, J4.3, U4.14 (BRIDGE_SPI_NSS)
BR_UART_CTS: J1.2, J2.2, U4.2 (BRIDGE_UART_CTS)
BR_UART_RTS: J1.3, J2.3, U4.3 (BRIDGE_UART_RTS)
BR_UART_RX: J1.1, J2.1, U4.1 (BRIDGE_UART_RX)
BR_UART_TX: J1.11, J2.11, U4.11 (BRIDGE_UART_TX)
GND: J1.5, J1.8, J2.5, J2.8, J5.5, J5.7, J5.8, J5.10, J6.5, J6.7, J6.8, J6.10, U4.5 (GNDDETECT), U4.8 (GND_2), U4.24 (GND), U4.26 (GND2), U4.27 (GND3), U4.29 (GND4)
JCLK/T_SWCLK: J1.13, J2.13, U4.13 (T_JCLK/T_SWCLK)
JTDI/NC: J5.9, J6.9, U4.28 (T_JTDI/NC)
JTDO/T_SWO: J1.6, J2.6, U4.6 (T_JTDO/T_SWO)
JTMS/T_SWDIO: J1.4, J2.4, U4.4 (T_JTMS/T_SWDIO)
NRST: J5.12, J6.12, U4.31 (T_NRST)
SW_DIR: J5.13, J6.13, U4.32 (T_SW_DIR)
VCP_RX: J3.2, J4.2, U4.15 (T_VCP_RX)
VCP_TX: J1.12, J2.12, U4.12 (T_VCP_TX)

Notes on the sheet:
Connectors
STLINK

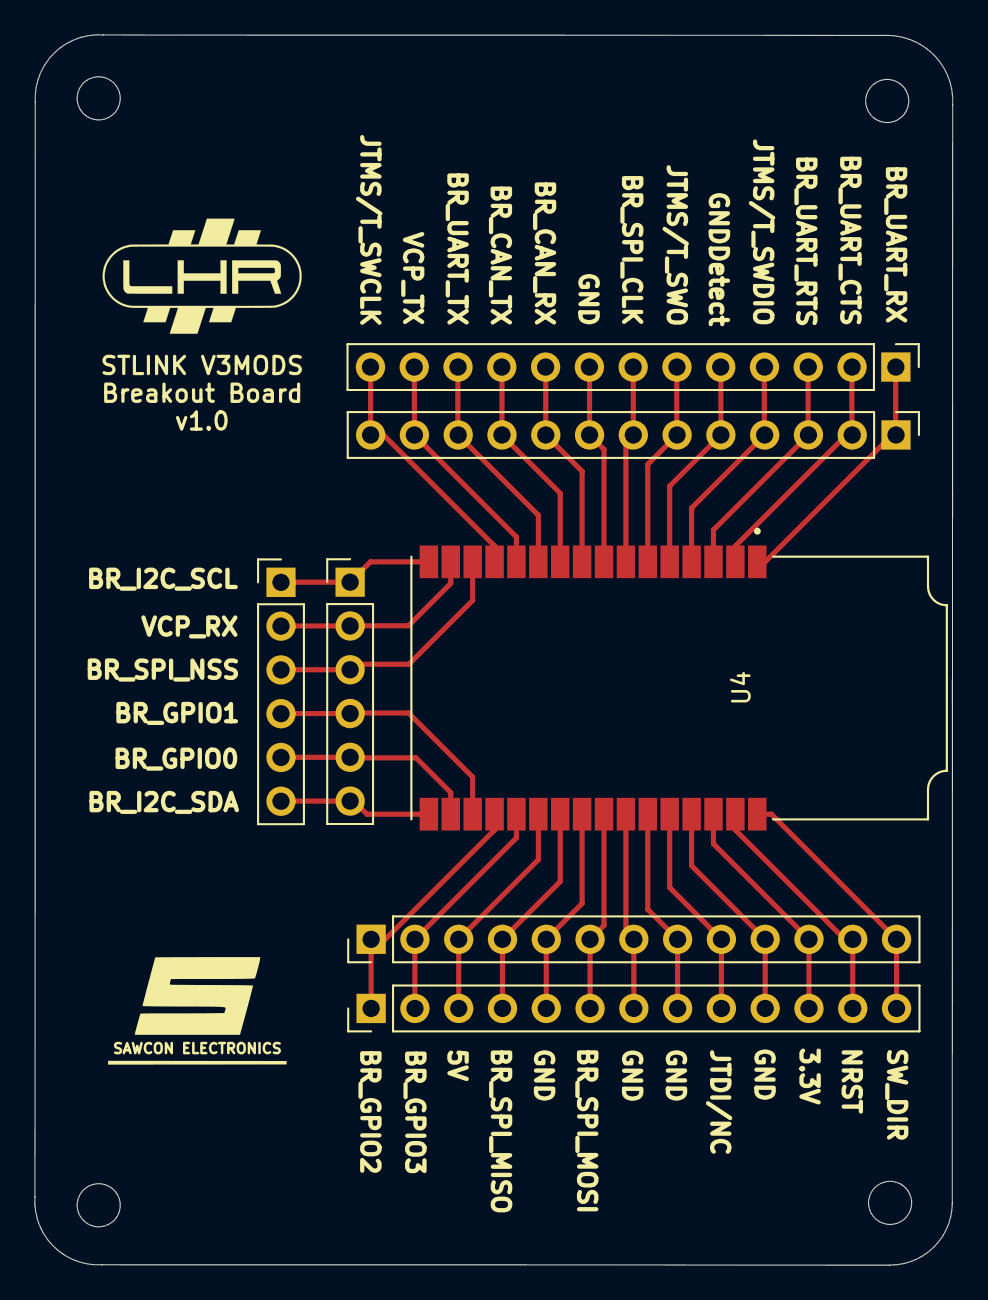
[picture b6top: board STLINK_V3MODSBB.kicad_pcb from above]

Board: 2 copper layers, 53.2 x 71.4 mm, 7 parts (0 on the bottom side), 27 nets.
